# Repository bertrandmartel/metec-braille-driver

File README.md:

# Metec Braille cell driver

Driver for [Metec Braille-line 20 Cell standard](http://web.metec-ag.de/downloads/braille-line-20cell.pdf) module for Arduino & Raspberry PI

This module is composed of 20 [B11 Metec Braille cells](http://web.metec-ag.de/downloads/b11b12-elektronik-1.pdf) driven by piezo-actuators which also feature one interaction button per cell (eg 20 buttons for this module). The module also needs a [DC/DC converter (5V to 200V)](http://web.metec-ag.de/downloads/dcdc-converter-5to200v.pdf)

This library is compatible with :

- [x] Arduino (tested on Uno & Mini)
- [x] Raspberry PI Linux & wiringPi library
- [x] Rapsberry PI Windows IoT core OS

This repo also includes an example using this driver and [liblouis](https://github.com/liblouis/liblouis) altogether on Raspberry PI (Linux/wiringPi)

## Wiring

### Arduino Uno

### Arduino Mini

### Raspberry PI

## Setup

```bash
git clone git@github.com:bertrandmartel/metec-braille-driver.git
cd metec-braille-driver
git submodule update --init --recursive
```

## Project structure

    .
    ├── src                              # library source
    ├── include                          # library includes
    ├── arduino      
    │   ├── arduino-makefile             # makefile for arduino (build environment)
    │   ├── examples                     # examples containing one folder per example
    │   └── Makefile                     # library Makefile (each sample call this Makefile)
    ├── raspberry      
    │   ├── linux-wiringpi               # Linux build with wiringPi library folder
    │   │   ├── examples                 # examples folder
    │   │   ├── raspberry-dev            # toolchain & wiringPi build using cmake
    │   │   ├── out                      # library output directory
    │   │   ├── out_liblouis             # liblouis output directory
    │   │   ├── CmakeList.txt            # cmake config for building MetecDriver and liblouis
    │   │   ├── liblouis_install.sh      # liblouis table install script (to run on Raspberry PI)
    │   │   ├── run.sh                   # build script
    │   │   └── clean.sh                 # clean raspberry pi folder (remove cache, output dir etc...)
    │   ├── windows-iot                  # Windows IoT core folder
    │   │   └── MetecDriver 
    │   │       ├── MetecDriverLibrary   # library project compiling C++/CX into Windows Runtime Component
    │   │       ├── ExampleButtonSimple  # buttons input example in C#
    │   │       ├── ExampleButtons       # buttons input + write pattern example in C#
    │   │       ├── ExamplePatternChange # change pattern every x sec example in C++
    │   │       ├── MultiCellsExample    # write multiple pattern example in C++
    │   │       └── SingleCellExample    # write single pattern example in C++
    │   └── liblouis                     # liblouis submodule build folder
    ├── 8pin-adapter                     # KiCad files for 2.00mm to 2.52mm 8 pin adapter
    └─── fritzing                        # Fritzing sketch for wiring pictures

## Library Usage

* **[Go to Arduino README](./arduino)**
* **[Go to Raspberry PI Linux + wiringPi README](./raspberry/linux-wiringpi)**
* **[Go to Raspberry PI Windows IoT Core README](./raspberry/windows-iot)**

## 8 Pin Adapter 

The 8 pin adapter 2.00mm to 2.54mm was created on [KiCad EDA](http://kicad.org/), files are available under `8pin-adapter` :

## Protocol

### Braille pattern

3 signals are used : 

* STRB (OUTPUT)
* CLK (OUTPUT)
* DIN (OUTPUT)

A shift register is used to write the Braille pattern, the data is written to DIN between each clock transition (data is written on CLK falling edge). All bit are latched on STRB falling edge.

The bit order for the Braille cell is the following XORed : 

You can use [this tool](https://bertrandmartel.github.io/braille-dot-converter/) to test values

For example the following write letter "V" aka ⠧ which is [BRAILLE-1236 in unicode](http://www.unicode.org/charts/PDF/U2800.pdf) : 

explanation for above : ⠧ gives 11000011 (XORed), bit order is 6/7/2/1/0/5/4/3 so it gives : 11011000, and XORed : 00100111

### Interaction buttons

3 signals are used : 

 * STRB (OUTPUT)
 * CLK (OUTPUT)
 * DOUT (INPUT)

The buttons can be read when strobe is high between each clock transtion (falling edge). B11 module can have 2 buttons so we need to read 20 * 2 times each time we check for button state :

explanation for above: the 2 last bit read are 01 which means the first button has been pressed 

## More resources

* This amazing post on Arduino forum : https://forum.arduino.cc/index.php?topic=236677.0 special thanks to metec_ab

* [dot converter tool](https://bertrandmartel.github.io/braille-dot-converter/) written in React JS is useful to quickly test a Braille pattern

* [liblouis](https://github.com/liblouis/liblouis) the open source Braille translator which can be used on Raspberry PI along with this driver (see Raspberry PI library usage)

* [Raspberry PI cross compile guide](https://medium.com/@au42/the-useful-raspberrypi-cross-compile-guide-ea56054de187)

* [raspberry-dev](https://github.com/bertrandmartel/raspberry-dev) : a quick development environment to develop for Raspberry PI

* [arduino-dev](https://github.com/bertrandmartel/arduino-makefile) for developping Arduino using a single Makefile

* [Fritzing parts](https://github.com/bertrandmartel/fritzing-parts) I've made for README aesthetics

## License

The MIT License (MIT) Copyright (c) 2018 Bertrand Martel

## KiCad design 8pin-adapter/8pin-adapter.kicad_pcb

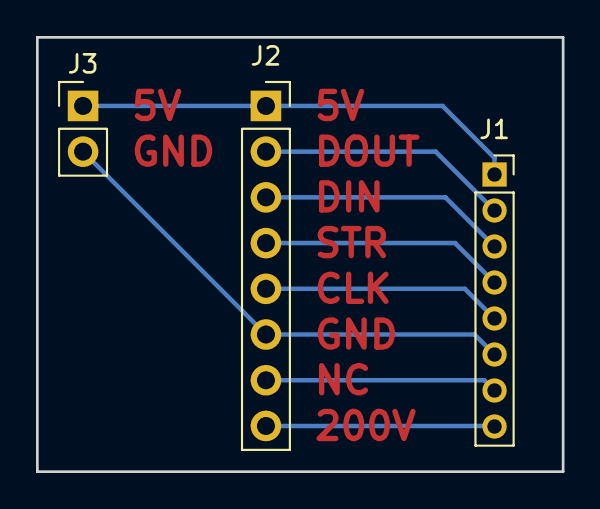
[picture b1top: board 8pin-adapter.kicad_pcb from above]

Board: 2 copper layers, 29.2 x 24.1 mm, 3 parts (0 on the bottom side), 8 nets.

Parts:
J1: Conn_01x08_Female; PinSocket_1x08_P2.00mm_Vertical
J2: Conn_01x08_Female; PinSocket_1x08_P2.54mm_Vertical
J3: Conn_01x02_Male; PinHeader_1x02_P2.54mm_Vertical

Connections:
/PIN1: J1.1, J2.1, J3.1
/PIN2: J1.2, J2.2
/PIN3: J1.3, J2.3
/PIN4: J1.4, J2.4
/PIN5: J1.5, J2.5
/PIN6: J1.6, J2.6, J3.2
/PIN7: J1.7, J2.7
/PIN8: J1.8, J2.8

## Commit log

2018-10-20 :sparkles: create repo metec-braille-driver
2018-10-20 :books: add license file
2018-10-20 :arrow_up: upgrade submodules
2018-10-20 :books: update README
2018-10-20 :wrench: remove library install configuration
2018-10-20 :wrench: fix liblouis build
2018-10-24 :sparkles: update windows build
2018-10-24 :checkered_flag: create windows runtime component
2018-10-24 :checkered_flag: C++/CX compatibility
2018-10-24 :books: add windows-iot examples in C# and C++ (background task)
2018-10-24 :arrow_up: update linux & arduino examples
2018-10-24 :sparkles: use uint16_t instead of double for windows build
2018-10-24 :checkered_flag: use only C# project examples referencing the C++ library
2018-10-24 :sparkles: update ignored files
2018-10-25 :books: update windows readme
2018-10-25 :sparkles: remove pch file
2018-10-25 :recycle: clean library folder
2018-10-25 :rocket: create nugget config
2018-10-25 :pencil: update ignored files
2018-10-25 :construction_worker: add appveyor config
2020-03-08 remove liblouis & raspberry-dev before adding them using download
2020-03-08 add raspberry-dev + auto download liblouis during build
2020-03-08 remove Makefile from git (autogenerated)
2020-03-09 fix write issues (cell data overlapping)
2020-03-09 remove useless delay & init strobe in checkButton
2020-03-09 disable button listener before writing cells and re-activate the listener after writing
2020-03-09 add bool accessor for windows
2020-03-09 fix travis script
2020-03-09 add missing submodule
2021-11-09 Update README.md
    https://forum.kicad.info/t/warning-avoid-all-links-to-kicad-pcb-org-use-kicad-org/31521
